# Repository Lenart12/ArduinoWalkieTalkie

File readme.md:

Arduino Walkie Talkie
===

## Scheme

---

## Scheme (KiCAD)

---

## PCB

---

Bill of materials
---

| Id | Designator                                                   | Package                                          | Quantity | Designation         | Supplier and ref |  |  | 
|------|----------------------------------------------------------------|----------------------------------------------------|------------|-----------------------|--------------------|--|--| 
| 1    | BZ1                                                          | BUZZER                                           | 1          | Buzzer              |                    |  |  | 
| 2    | R4,R3                                                        | R_Axial_DIN0207_L6.3mm_D2.5mm_P7.62mm_Horizontal | 2          | 1k5                 |                    |  |  | 
| 3    | R2                                                           | R_Axial_DIN0207_L6.3mm_D2.5mm_P7.62mm_Horizontal | 1          | 15k                 |                    |  |  | 
| 4    | R1,R6,R8                                                     | R_Axial_DIN0207_L6.3mm_D2.5mm_P7.62mm_Horizontal | 3          | 10k                 |                    |  |  | 
| 5    | R5                                                           | R_Axial_DIN0207_L6.3mm_D2.5mm_P7.62mm_Horizontal | 1          | 4.7k                |                    |  |  | 
| 6    | R7                                                           | R_Axial_DIN0207_L6.3mm_D2.5mm_P7.62mm_Horizontal | 1          | 2k2                 |                    |  |  | 
| 7    | R9                                                           | R_Axial_DIN0207_L6.3mm_D2.5mm_P7.62mm_Horizontal | 1          | 220                 |                    |  |  | 
| 8    | A1                                                           | Arduino_Nano                                     | 1          | Arduino_Nano_v3.x   |                    |  |  | 
| 9    | BMP1                                                         | BMP280                                           | 1          | BMP280              |                    |  |  | 
| 10   | BT1                                                          | BAT_LIION_3V7                                    | 1          | Battery             |                    |  |  | 
| 11   | CC1                                                          | DD05CVSA                                         | 1          | DD05CVSA            |                    |  |  | 
| 12   | D1                                                           | D_DO-35_SOD27_P7.62mm_Horizontal                 | 1          | 1N4148              |                    |  |  | 
| 13   | JP1                                                          | PIN_JUMPER                                       | 1          | Jumper              |                    |  |  | 
| 14   | SW1,SW2,SW3,SW4,SW5,SW6,SW7,SW8,SW9,SW10,SW11,SW12,SW13,SW14 | SW_TH_Tactile_Omron_B3F-10xx                     | 14         | SW_Push_Dual        |                    |  |  | 
| 15   | TFT1                                                         | TFT_KMR_1.8_SPI                                  | 1          | 1.8_SPI_TFT_128*160 |                    |  |  | 
| 16   | U1                                                           | nRF24L01_Breakout                                | 1          | NRF24L01_Breakout   |                    |  |  | 

---

License
---
"THE BEER-WARE LICENSE" (Revision 42): koslenart@gmail.com wrote this file. As long as you retain this notice you can do whatever you want with this stuff. If we meet some day, and you think this stuff is worth it, you can buy me a beer in return Poul-Henning Kamp

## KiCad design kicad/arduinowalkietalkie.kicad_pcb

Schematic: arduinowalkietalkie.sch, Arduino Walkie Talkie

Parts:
A1: Arduino_Nano_v3.x; Arduino_Nano
BMP1: BMP280
BT1: Battery; BAT_LIION_3V7
BZ1: Buzzer; BUZZER
C1, C2, C3, C4: C; C_Disc_D4.7mm_W2.5mm_P5.00mm
CC1: DD05CVSA
D1: 1N4148; D_DO-35_SOD27_P7.62mm_Horizontal
JP1, JP2: Jumper; PIN_JUMPER
R1, R6, R8: 10k; R_Axial_DIN0207_L6.3mm_D2.5mm_P7.62mm_Horizontal
R2: 15k; R_Axial_DIN0207_L6.3mm_D2.5mm_P7.62mm_Horizontal
R3, R4: 1k5; R_Axial_DIN0207_L6.3mm_D2.5mm_P7.62mm_Horizontal
R5: 4.7k; R_Axial_DIN0207_L6.3mm_D2.5mm_P7.62mm_Horizontal
R7: 2k2; R_Axial_DIN0207_L6.3mm_D2.5mm_P7.62mm_Horizontal
R9, R15: 220; R_Axial_DIN0207_L6.3mm_D2.5mm_P7.62mm_Horizontal
R10, R11, R12, R13, R14: 2k7; R_Axial_DIN0207_L6.3mm_D2.5mm_P7.62mm_Horizontal
R16: 10K; R_Axial_DIN0207_L6.3mm_D2.5mm_P7.62mm_Horizontal
SW1, SW2, SW3, SW4, SW5, SW6, SW7, SW8, SW9, SW10, SW11, SW12, SW13, SW14: SW_Push_Dual; SW_TH_Tactile_Omron_B3F-10xx
TFT1: 1.8_SPI_TFT_128*160; TFT_KMR_1.8_SPI
U1: NRF24L01_Breakout; nRF24L01_Breakout

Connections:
+5V: A1.27, BMP1.1 (VIN), C1.1, C2.1, C3.1, C4.1, D1.1, JP2.1, R8.1, SW1.1, SW10.1
GND: A1.29, BMP1.2 (GND), BZ1.2, C1.2, C2.2, C3.2, C4.2, CC1.2 (GND), R1.2, R6.1, R7.2, SW11.2, SW12.2, SW13.2, SW14.2, TFT1.1 (LED-), TFT1.16 (GND), U1.1
MISO: A1.15, U1.7
MOSI: A1.14, U1.6
unnamed: A1.5, SW10.4
unnamed: A1.6, SW1.4
unnamed: A1.7, R15.1
unnamed: A1.8, R9.2
unnamed: A1.9, U1.4
unnamed: A1.10, U1.3
unnamed: A1.11, R13.2
unnamed: A1.12, R14.2
unnamed: A1.13, R10.2
unnamed: A1.17, TFT1.15 (VCC), U1.2
unnamed: A1.19, R4.2, R8.2, SW5.3, SW9.3, SW14.3
unnamed: A1.20, R16.2
unnamed: A1.21, R11.2
unnamed: A1.22, R12.2
unnamed: BT1.1, CC1.3 (BAT), R16.1
unnamed: BT1.2, CC1.4 (GND)
unnamed: BZ1.1, R15.2
unnamed: CC1.1 (VIN), JP2.2
unnamed: CC1.6 (VOUT), JP1.1
unnamed: D1.2, JP1.2
unnamed: R1.1, SW1.3
unnamed: R2.1, SW2.3, SW6.3, SW11.3
unnamed: R2.2, R3.1, SW3.3, SW7.3, SW12.3
unnamed: R3.2, R4.1, SW4.3, SW8.3, SW13.3
unnamed: R5.1, R7.1, SW6.2, SW7.2, SW8.2, SW9.2
unnamed: R5.2, SW2.2, SW3.2, SW4.2, SW5.2
unnamed: R6.2, SW10.3
unnamed: R9.1, TFT1.2 (LED+)
unnamed: R10.1, TFT1.7 (TFT_CS)
unnamed: R11.1, TFT1.8 (TFT_SCK)
unnamed: R12.1, TFT1.9 (TFT_MOSI)
unnamed: R13.1, TFT1.10 (TFT_DC)
unnamed: R14.1, TFT1.11 (TFT_RST)
SCK: A1.16, U1.5
SCL: A1.24, BMP1.3 (SCL)
SDA: A1.23, BMP1.4 (SDA)

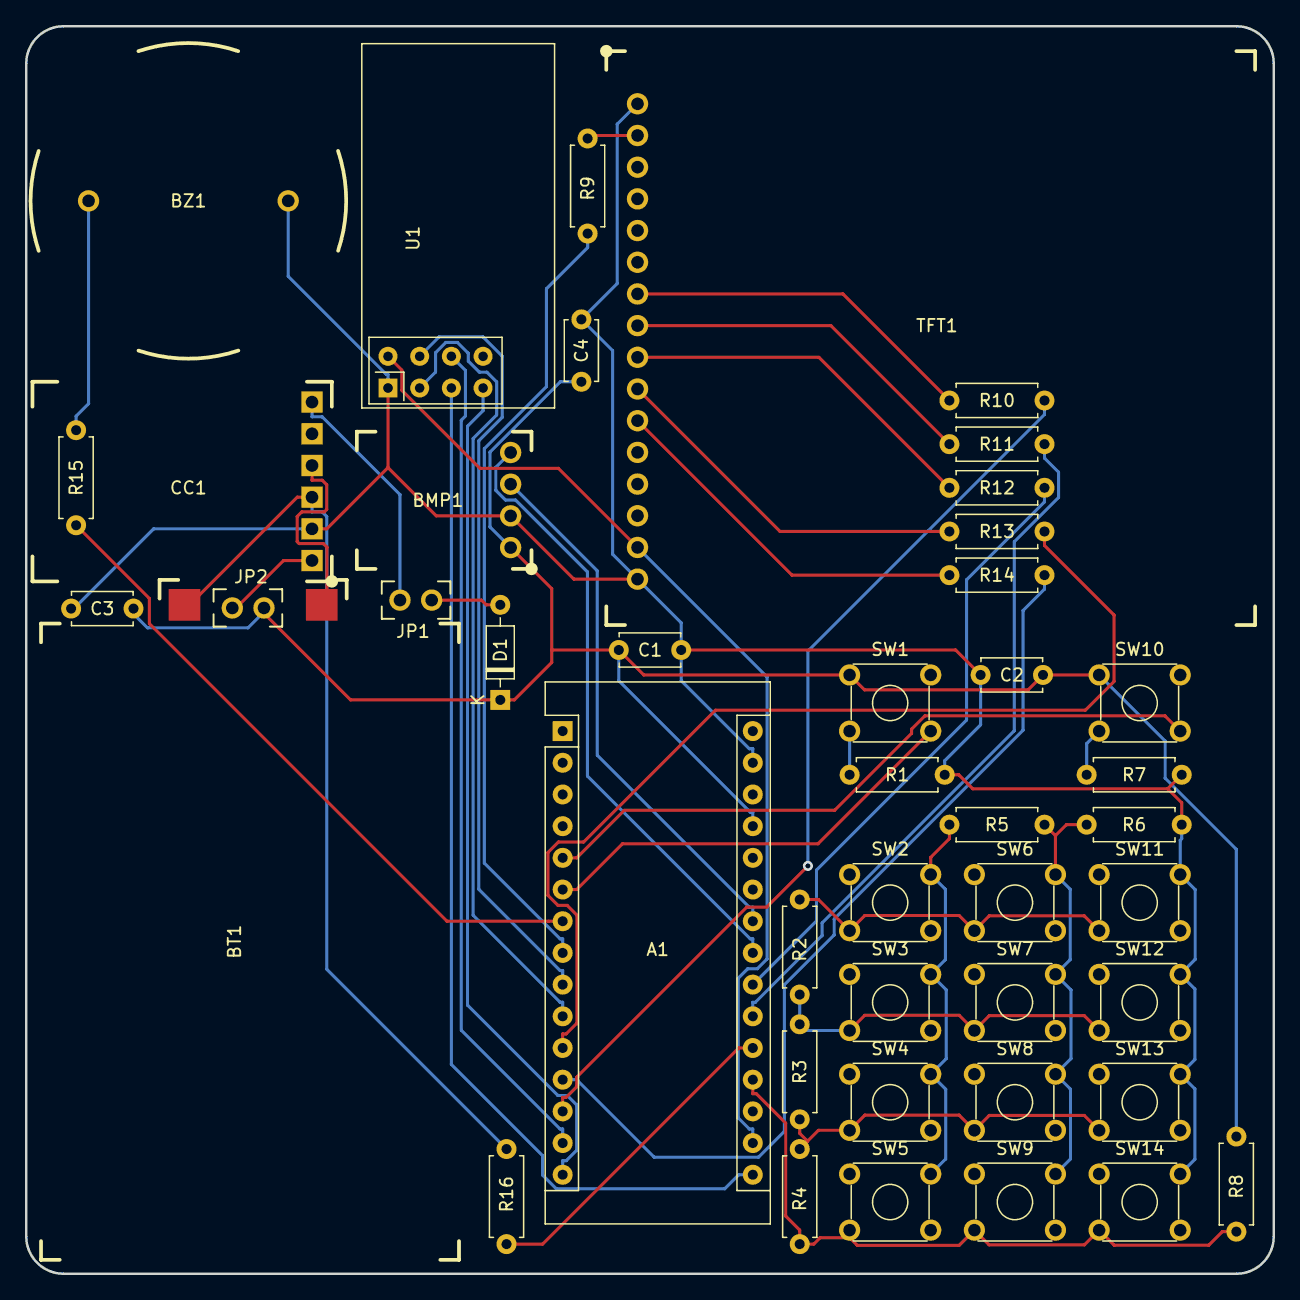
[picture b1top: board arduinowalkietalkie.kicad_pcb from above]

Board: 2 copper layers, 100.0 x 100.0 mm, 44 parts (0 on the bottom side), 40 nets.

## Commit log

2019-02-06 inital commit
2019-02-07 Kicad lcd symbol
2019-02-08 skematic
2019-02-08 gerber file
2019-02-08 compacted pcb to 100mmx100mm
2019-02-23 update pcb
2019-04-03 New pcb
2019-05-07 V0.2
2019-05-07 V0.1 files

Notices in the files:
kicad/arduinowalkietalkie.sch:
License: Beerware rev42
